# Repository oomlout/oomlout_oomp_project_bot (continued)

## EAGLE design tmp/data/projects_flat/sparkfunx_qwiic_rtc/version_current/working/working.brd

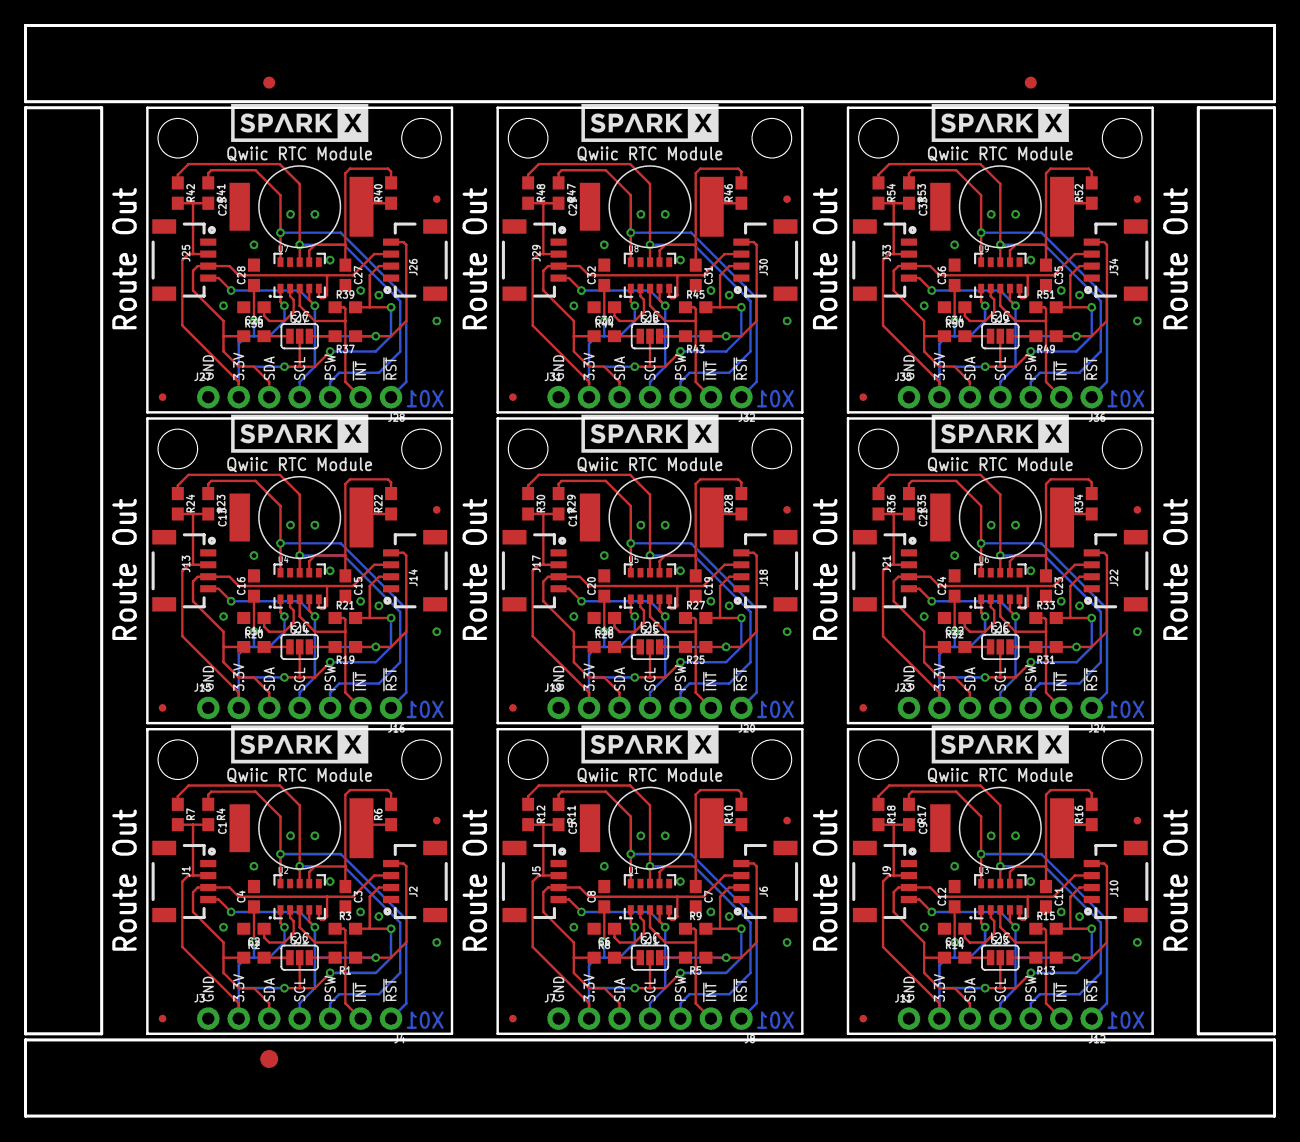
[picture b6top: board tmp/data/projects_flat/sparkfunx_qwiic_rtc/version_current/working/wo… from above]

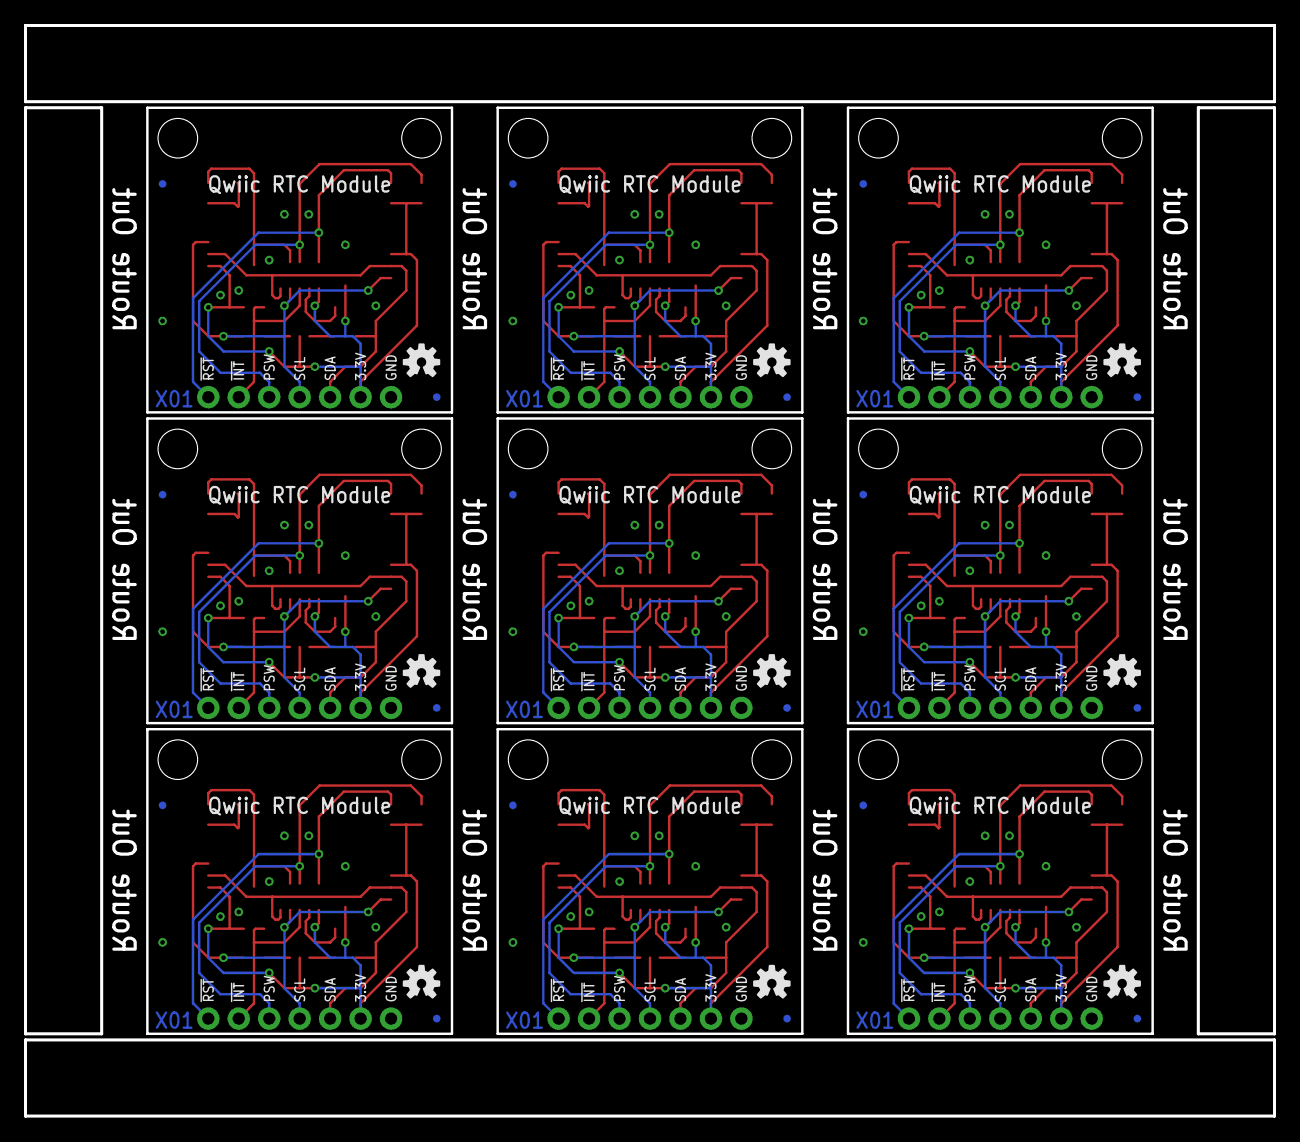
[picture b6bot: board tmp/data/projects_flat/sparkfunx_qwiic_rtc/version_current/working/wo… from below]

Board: 2 copper layers, 104.1 x 90.9 mm, 219 parts (27 on the bottom side), 108 nets.

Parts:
C1, C5, C9, C13, C17, C21, C25, C29, C33: .22F-SUPERCAP; DSK-RADIAL-6.8MM
C2, C6, C10, C14, C18, C22, C26, C30, C34: 47pF; 0603
C3, C4, C7, C8, C11, C12, C15, C16, C19, C20, C23, C24, C27, C28, C31, C32, C35, C36: 10nF; 0603
E$1, E$2: FIDUCIAL-1X2
E$3: FIDUCIAL-1.5X3
FD1, FD2, FD3, FD4, FD5, FD6, FD7, FD8, FD9, FD10, FD11, FD12, FD13, FD14, FD15, FD16, FD17, FD18, FD19, FD20, FD21, FD22, FD23, FD24, FD25, FD26, FD27, FD28, FD29, FD30, FD31, FD32, FD33, FD34, FD35, FD36: FIDUCIALUFIDUCIAL; FIDUCIAL-MICRO
J1, J2, J5, J6, J9, J10, J13, J14, J17, J18, J21, J22, J25, J26, J29, J30, J33, J34: SMD; 1X04_1MM_RA
J3, J7, J11, J15, J19, J23, J27, J31, J35: PTH; 1X04_NO_SILK
J4, J8, J12, J16, J20, J24, J28, J32, J36: 1X03_NO_SILK
LOGO1, LOGO2, LOGO3, LOGO4, LOGO5, LOGO6, LOGO7, LOGO8, LOGO9: OSHW-LOGOS; OSHW-LOGO-S
R1, R2, R5, R8, R13, R14, R19, R20, R25, R26, R31, R32, R37, R38, R43, R44, R49, R50: 2.2k; 0603
R3, R4, R7, R9, R11, R12, R15, R17, R18, R21, R23, R24, R27, R29, R30, R33, R35, R36, R39, R41, R42, R45, R47, R48, R51, R53, R54: 10k; 0603
R6, R10, R16, R22, R28, R34, R40, R46, R52: 1K; 0603
SJ1, SJ2, SJ3, SJ4, SJ5, SJ6, SJ7, SJ8, SJ9: JUMPER-SMT_3_2-NC_PASTE_SILK; SMT-JUMPER_3_2-NC_PASTE_SILK
U1, U2, U3, U4, U5, U6, U7, U8, U9: RV-1805
U$1, U$4, U$9, U$12, U$15, U$18, U$21, U$24, U$27: SPARKX-LOGO5; SPARKX-LARGE
U$2, U$3, U$5, U$6, U$7, U$8, U$10, U$11, U$13, U$14, U$16, U$17, U$19, U$20, U$22, U$23, U$25, U$26: STAND-OFF

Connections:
3.3V: C4.1, J1.2, J2.2, J3.2, R3.2, R4.2, R7.2, SJ2.2, U2.1
3.3V1: C8.1, J5.2, J6.2, J7.2, R9.2, R11.2, R12.2, SJ1.2, U1.1
3.3V2: C12.1, J9.2, J10.2, J11.2, R15.2, R17.2, R18.2, SJ3.2, U3.1
3.3V3: C16.1, J13.2, J14.2, J15.2, R21.2, R23.2, R24.2, SJ4.2, U4.1
3.3V4: C20.1, J17.2, J18.2, J19.2, R27.2, R29.2, R30.2, SJ5.2, U5.1
3.3V5: C24.1, J21.2, J22.2, J23.2, R33.2, R35.2, R36.2, SJ6.2, U6.1
3.3V6: C28.1, J25.2, J26.2, J27.2, R39.2, R41.2, R42.2, SJ7.2, U7.1
3.3V7: C32.1, J29.2, J30.2, J31.2, R45.2, R47.2, R48.2, SJ8.2, U8.1
3.3V8: C36.1, J33.2, J34.2, J35.2, R51.2, R53.2, R54.2, SJ9.2, U9.1
!INT: J4.2, R3.1, U2.3
!INT1: J8.2, R9.1, U1.3
!INT2: J12.2, R15.1, U3.3
!INT3: J16.2, R21.1, U4.3
!INT4: J20.2, R27.1, U5.3
!INT5: J24.2, R33.1, U6.3
!INT6: J28.2, R39.1, U7.3
!INT7: J32.2, R45.1, U8.3
!INT8: J36.2, R51.1, U9.3
!RST: J4.1, R4.1, U2.10
!RST1: J8.1, R11.1, U1.10
!RST2: J12.1, R17.1, U3.10
!RST3: J16.1, R23.1, U4.10
!RST4: J20.1, R29.1, U5.10
!RST5: J24.1, R35.1, U6.10
!RST6: J28.1, R41.1, U7.10
!RST7: J32.1, R47.1, U8.10
!RST8: J36.1, R53.1, U9.10
GND: C1.-, C2.2, C3.2, C4.2, J1.1, J2.1, J3.1, U2.6, U2.9
GND1: C5.-, C6.2, C7.2, C8.2, J5.1, J6.1, J7.1, U1.6, U1.9
GND2: C9.-, C10.2, C11.2, C12.2, J9.1, J10.1, J11.1, U3.6, U3.9
GND3: C13.-, C14.2, C15.2, C16.2, J13.1, J14.1, J15.1, U4.6, U4.9
GND4: C17.-, C18.2, C19.2, C20.2, J17.1, J18.1, J19.1, U5.6, U5.9
GND5: C21.-, C22.2, C23.2, C24.2, J21.1, J22.1, J23.1, U6.6, U6.9
GND6: C25.-, C26.2, C27.2, C28.2, J25.1, J26.1, J27.1, U7.6, U7.9
GND7: C29.-, C30.2, C31.2, C32.2, J29.1, J30.1, J31.1, U8.6, U8.9
GND8: C33.-, C34.2, C35.2, C36.2, J33.1, J34.1, J35.1, U9.6, U9.9
unnamed: R1.2, SJ2.3
unnamed: R2.2, SJ2.1
unnamed: R5.2, SJ1.3
unnamed: C2.1, U2.2
unnamed: C1.+, R6.1
unnamed: R8.2, SJ1.1
unnamed: C6.1, U1.2
unnamed: C5.+, R10.1
unnamed: R13.2, SJ3.3
unnamed: R14.2, SJ3.1
unnamed: C10.1, U3.2
unnamed: C9.+, R16.1
unnamed: R19.2, SJ4.3
unnamed: R20.2, SJ4.1
unnamed: C14.1, U4.2
unnamed: C13.+, R22.1
unnamed: R25.2, SJ5.3
unnamed: R26.2, SJ5.1
unnamed: C18.1, U5.2
unnamed: C17.+, R28.1
unnamed: R31.2, SJ6.3
unnamed: R32.2, SJ6.1
unnamed: C22.1, U6.2
unnamed: C21.+, R34.1
unnamed: R37.2, SJ7.3
unnamed: R38.2, SJ7.1
unnamed: C26.1, U7.2
unnamed: C25.+, R40.1
unnamed: R43.2, SJ8.3
unnamed: R44.2, SJ8.1
unnamed: C30.1, U8.2
unnamed: C29.+, R46.1
unnamed: R49.2, SJ9.3
unnamed: R50.2, SJ9.1
unnamed: C34.1, U9.2
unnamed: C33.+, R52.1
PSW: J4.3, R7.1, U2.8
PSW1: J8.3, R12.1, U1.8
PSW2: J12.3, R18.1, U3.8
PSW3: J16.3, R24.1, U4.8
PSW4: J20.3, R30.1, U5.8
PSW5: J24.3, R36.1, U6.8
PSW6: J28.3, R42.1, U7.8
PSW7: J32.3, R48.1, U8.8
PSW8: J36.3, R54.1, U9.8
SCL: J1.4, J2.4, J3.4, R1.1, U2.4
SCL1: J5.4, J6.4, J7.4, R5.1, U1.4
SCL2: J9.4, J10.4, J11.4, R13.1, U3.4
SCL3: J13.4, J14.4, J15.4, R19.1, U4.4
SCL4: J17.4, J18.4, J19.4, R25.1, U5.4
SCL5: J21.4, J22.4, J23.4, R31.1, U6.4
SCL6: J25.4, J26.4, J27.4, R37.1, U7.4
SCL7: J29.4, J30.4, J31.4, R43.1, U8.4
SCL8: J33.4, J34.4, J35.4, R49.1, U9.4
SDA: J1.3, J2.3, J3.3, R2.1, U2.5
SDA1: J5.3, J6.3, J7.3, R8.1, U1.5
SDA2: J9.3, J10.3, J11.3, R14.1, U3.5
SDA3: J13.3, J14.3, J15.3, R20.1, U4.5
SDA4: J17.3, J18.3, J19.3, R26.1, U5.5
SDA5: J21.3, J22.3, J23.3, R32.1, U6.5
SDA6: J25.3, J26.3, J27.3, R38.1, U7.5
SDA7: J29.3, J30.3, J31.3, R44.1, U8.5
SDA8: J33.3, J34.3, J35.3, R50.1, U9.5
VBACKUP: C3.1, R6.2, U2.7
VBACKUP1: C7.1, R10.2, U1.7
VBACKUP2: C11.1, R16.2, U3.7
VBACKUP3: C15.1, R22.2, U4.7
VBACKUP4: C19.1, R28.2, U5.7
VBACKUP5: C23.1, R34.2, U6.7
VBACKUP6: C27.1, R40.2, U7.7
VBACKUP7: C31.1, R46.2, U8.7
VBACKUP8: C35.1, R52.2, U9.7

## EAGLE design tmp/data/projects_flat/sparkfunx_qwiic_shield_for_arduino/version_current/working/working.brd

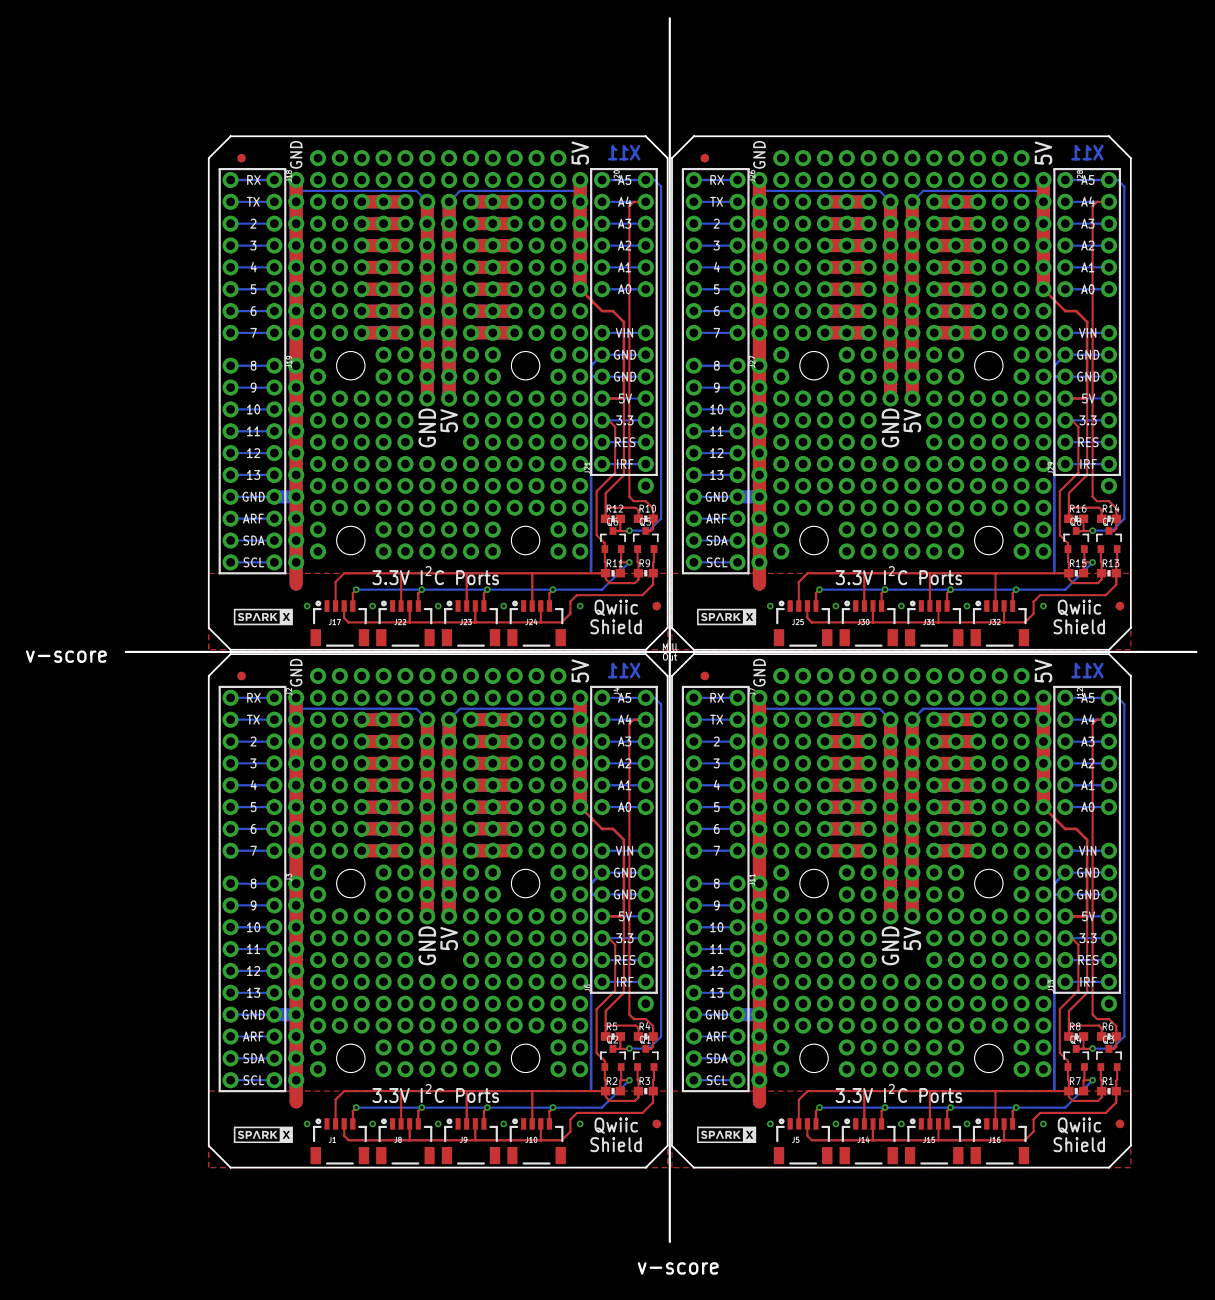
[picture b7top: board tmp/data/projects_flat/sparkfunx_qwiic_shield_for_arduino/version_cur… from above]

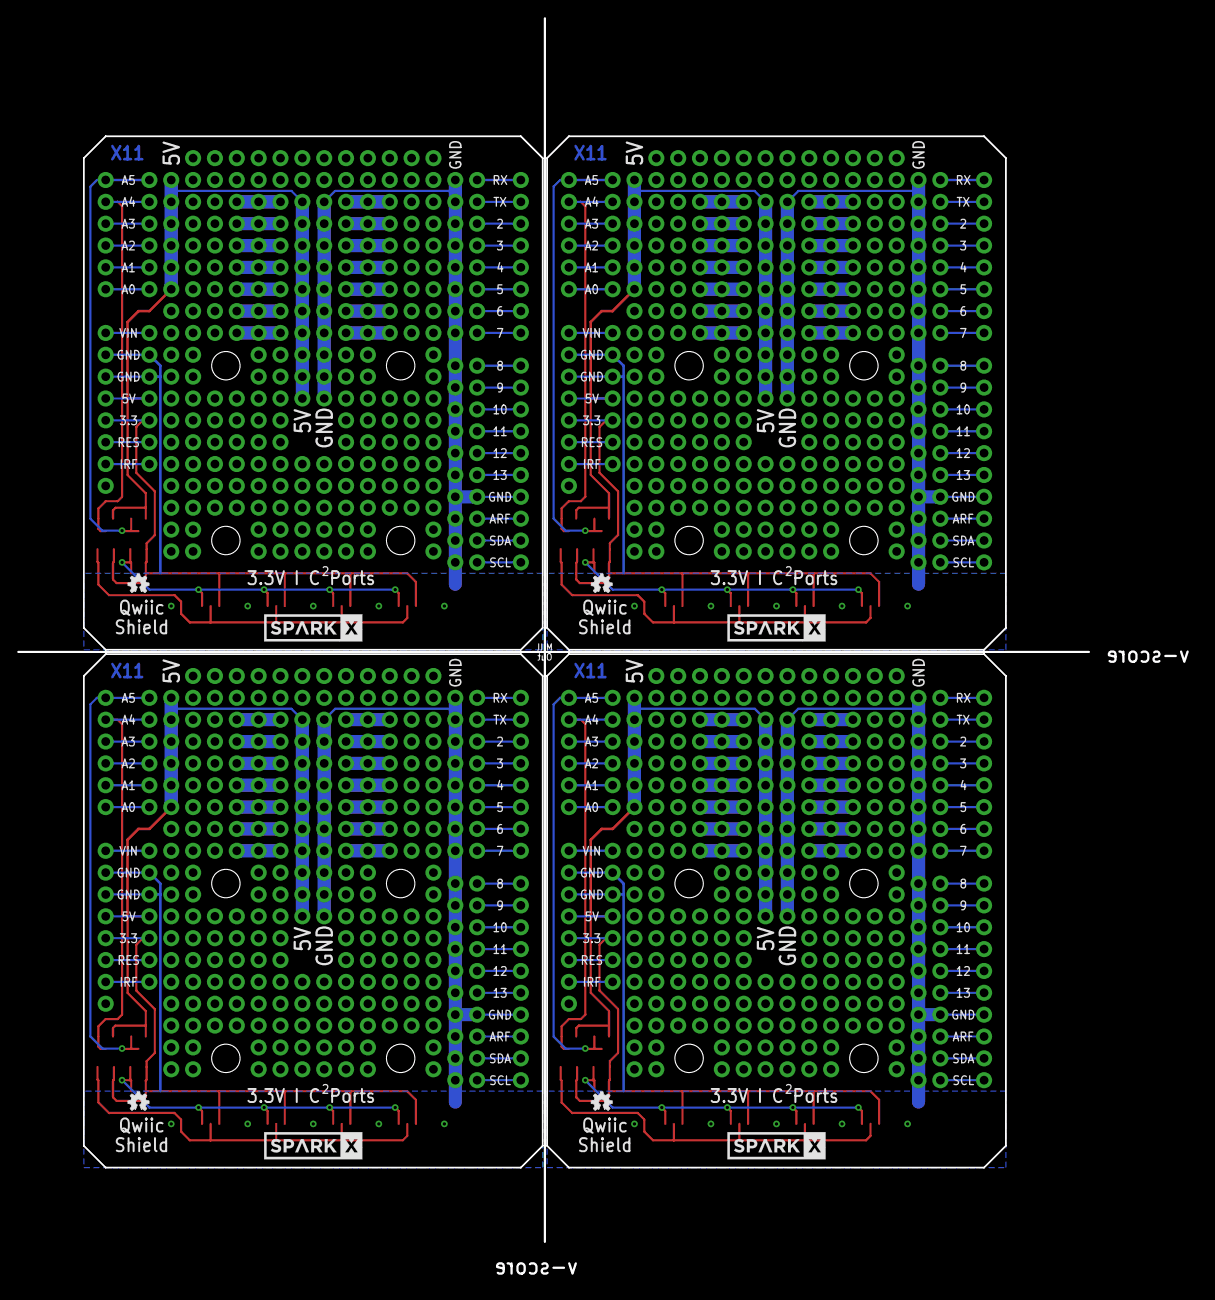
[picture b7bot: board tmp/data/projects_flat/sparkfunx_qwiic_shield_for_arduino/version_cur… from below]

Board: 2 copper layers, 124.5 x 142.2 mm, 84 parts (8 on the bottom side), 124 nets.

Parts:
FD1, FD2, FD3, FD4, FD5, FD6, FD7, FD8: FIDUCIAL1X2; FIDUCIAL-1X2
J1, J5, J8, J9, J10, J14, J15, J16, J17, J22, J23, J24, J25, J30, J31, J32: 1X04_1MM_RA
J2, J7, J18, J26: 1X08_NO_SILK
J3, J11, J19, J27: 1X10_NO_SILK
J4, J12, J20, J28: 1X06_NO_SILK
J6, J13, J21, J29: 1X07_NO_SILK
LOGO1, LOGO2, LOGO3, LOGO4: OSHW-LOGOMINI; OSHW-LOGO-MINI
Q1, Q2, Q3, Q4, Q5, Q6, Q7, Q8: 200mA/50V; SOT23-3
R1, R2, R3, R4, R5, R6, R7, R8, R9, R10, R11, R12, R13, R14, R15, R16: 4.7K; 0603-RES
U1, U2, U3, U4: ARDUINO UNO; UNO_R3_SHIELD_NOLABELS
U$1, U$4, U$7, U$10: SPARKX-LOGO3; SPARKX-SMALL
U$2, U$5, U$8, U$11: SPARKX-LOGO5; SPARKX-LARGE
U$3, U$6, U$9, U$12: QWIIC_BOARD_OUTLINEH; QWIIC_BOARD_MOUNT_HOLES

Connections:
3.3V: J1.2, J6.3, J8.2, J9.2, J10.2, Q1.1, Q2.1, R2.1, R3.1, U1.3.3V
3.3V1: J5.2, J13.3, J14.2, J15.2, J16.2, Q3.1, Q4.1, R1.1, R7.1, U2.3.3V
3.3V2: J17.2, J21.3, J22.2, J23.2, J24.2, Q5.1, Q6.1, R9.1, R11.1, U3.3.3V
3.3V3: J25.2, J29.3, J30.2, J31.2, J32.2, Q7.1, Q8.1, R13.1, R15.1, U4.3.3V
5V: J6.4, R4.1, R5.1, U1.5V
5V1: J13.4, R6.1, R8.1, U2.5V
5V2: J21.4, R10.1, R12.1, U3.5V
5V3: J29.4, R14.1, R16.1, U4.5V
A0: J4.6, U1.A0
A1: J4.5, U1.A1
A2: J4.4, U1.A2
A3: J4.3, U1.A3
A4: J12.3, U2.A3
A5: J12.4, U2.A2
A6: J12.5, U2.A1
A7: J12.6, U2.A0
A8: J20.3, U3.A3
A9: J20.4, U3.A2
A10: J20.5, U3.A1
A11: J20.6, U3.A0
A12: J28.3, U4.A3
A13: J28.4, U4.A2
A14: J28.5, U4.A1
A15: J28.6, U4.A0
AREF: J3.8, U1.AREF
AREF1: J11.8, U2.AREF
AREF2: J19.8, U3.AREF
AREF3: J27.8, U4.AREF
D1: J7.3, U2.D2
D2: J2.3, U1.D2
D3: J2.4, U1.D3
D4: J2.5, U1.D4
D5: J2.6, U1.D5
D6: J2.7, U1.D6
D7: J2.8, U1.D7
D8: J3.1, U1.D8
D9: J3.2, U1.D9
D10: J3.3, U1.D10
D11: J3.4, U1.D11
D12: J3.5, U1.D12
D13: J3.6, U1.D13
D14: J7.4, U2.D3
D15: J7.5, U2.D4
D16: J7.6, U2.D5
D17: J7.7, U2.D6
D18: J7.8, U2.D7
D19: J11.1, U2.D8
D20: J11.2, U2.D9
D21: J11.3, U2.D10
D22: J11.4, U2.D11
D23: J11.5, U2.D12
D24: J11.6, U2.D13
D25: J18.3, U3.D2
D26: J18.4, U3.D3
D27: J18.5, U3.D4
D28: J18.6, U3.D5
D29: J18.7, U3.D6
D30: J18.8, U3.D7
D31: J19.1, U3.D8
D32: J19.2, U3.D9
D33: J19.3, U3.D10
D34: J19.4, U3.D11
D35: J19.5, U3.D12
D36: J19.6, U3.D13
D37: J26.3, U4.D2
D38: J26.4, U4.D3
D39: J26.5, U4.D4
D40: J26.6, U4.D5
D41: J26.7, U4.D6
D42: J26.8, U4.D7
D43: J27.1, U4.D8
D44: J27.2, U4.D9
D45: J27.3, U4.D10
D46: J27.4, U4.D11
D47: J27.5, U4.D12
D48: J27.6, U4.D13
GND: J1.1, J3.7, J6.5, J6.6, J8.1, J9.1, J10.1, U1.GND@0, U1.GND@1, U1.GND@2
GND1: J5.1, J11.7, J13.5, J13.6, J14.1, J15.1, J16.1, U2.GND@0, U2.GND@1, U2.GND@2
GND2: J17.1, J19.7, J21.5, J21.6, J22.1, J23.1, J24.1, U3.GND@0, U3.GND@1, U3.GND@2
GND3: J25.1, J27.7, J29.5, J29.6, J30.1, J31.1, J32.1, U4.GND@0, U4.GND@1, U4.GND@2
HV_SCL: J4.1, Q2.3, R5.2, U1.A5
HV_SCL1: J12.1, Q4.3, R8.2, U2.A5
HV_SCL2: J20.1, Q6.3, R12.2, U3.A5
HV_SCL3: J28.1, Q8.3, R16.2, U4.A5
HV_SDA: J4.2, Q1.3, R4.2, U1.A4
HV_SDA1: J12.2, Q3.3, R6.2, U2.A4
HV_SDA2: J20.2, Q5.3, R10.2, U3.A4
HV_SDA3: J28.2, Q7.3, R14.2, U4.A4
IOREF: J6.1, U1.IOREF
IOREF1: J13.1, U2.IOREF
IOREF2: J21.1, U3.IOREF
IOREF3: J29.1, U4.IOREF
RES: J6.2, U1.RES
RES1: J13.2, U2.RES
RES2: J21.2, U3.RES
RES3: J29.2, U4.RES
RX: J2.1, U1.RX
RX1: J7.1, U2.RX
RX2: J18.1, U3.RX
RX3: J26.1, U4.RX
SCL: J1.4, J8.4, J9.4, J10.4, Q2.2, R2.2
SCL1: J3.10, U1.SCL
SCL2: J5.4, J14.4, J15.4, J16.4, Q4.2, R7.2
SCL3: J11.10, U2.SCL
SCL4: J17.4, J22.4, J23.4, J24.4, Q6.2, R11.2
SCL5: J19.10, U3.SCL
SCL6: J25.4, J30.4, J31.4, J32.4, Q8.2, R15.2
SCL7: J27.10, U4.SCL
SDA: J1.3, J8.3, J9.3, J10.3, Q1.2, R3.2
SDA1: J3.9, U1.SDA
SDA2: J5.3, J14.3, J15.3, J16.3, Q3.2, R1.2
SDA3: J11.9, U2.SDA
SDA4: J17.3, J22.3, J23.3, J24.3, Q5.2, R9.2
SDA5: J19.9, U3.SDA
SDA6: J25.3, J30.3, J31.3, J32.3, Q7.2, R13.2
SDA7: J27.9, U4.SDA
TX: J2.2, U1.TX
TX1: J7.2, U2.TX
TX2: J18.2, U3.TX
TX3: J26.2, U4.TX
VIN: J6.7, U1.VIN
VIN1: J13.7, U2.VIN
VIN2: J21.7, U3.VIN
VIN3: J29.7, U4.VIN
